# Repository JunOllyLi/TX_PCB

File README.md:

NOTE: the latest PCB had been manufactured was v2.0. But it had the Gimbal ZH-connector reversed. The schematics and PCB drawing had been updated to v2.1 to fix that. But v2.1 had not been really manufactured yet.

By default, Muffin is designed to use FlySky hall gimblal, over UART. However, if any other gimbals can be used with two wires (4 including GND and 3.3V), SW can be modified to use that.

Two RF module interfaces were designed. Although the name of them are for INTMOD and EXTMOD, SW can totally choose how they were used. The default configuration has the ELRS module connected to INTMOD and 4in1 connected to EXTMOD.

Those two modules have their own individual 5V power supply, controled by SW.
The PPM in/out on the back of FS6 shares the same signal pins of the EXTMOD.

And again, although the default design for them are UART and PPM, SW can totally choose other two wires protocol. ESP32 is very flexible regarding pin muxing.

# BOM (parts not listed in the schematics)
+ display module: IL9488 https://www.aliexpress.us/item/3256803764394132.html?spm=a2g0o.order_list.order_list_main.46.48c41802DB5b2D&gatewayAdapt=glo2usa
+ CPU ESP32S3 N16R8: https://www.aliexpress.us/item/3256805164206118.html?spm=a2g0o.order_list.order_list_main.61.48c41802DB5b2D&gatewayAdapt=glo2usa
+ Zorro 4in1 module
+ Zorro ELRS module

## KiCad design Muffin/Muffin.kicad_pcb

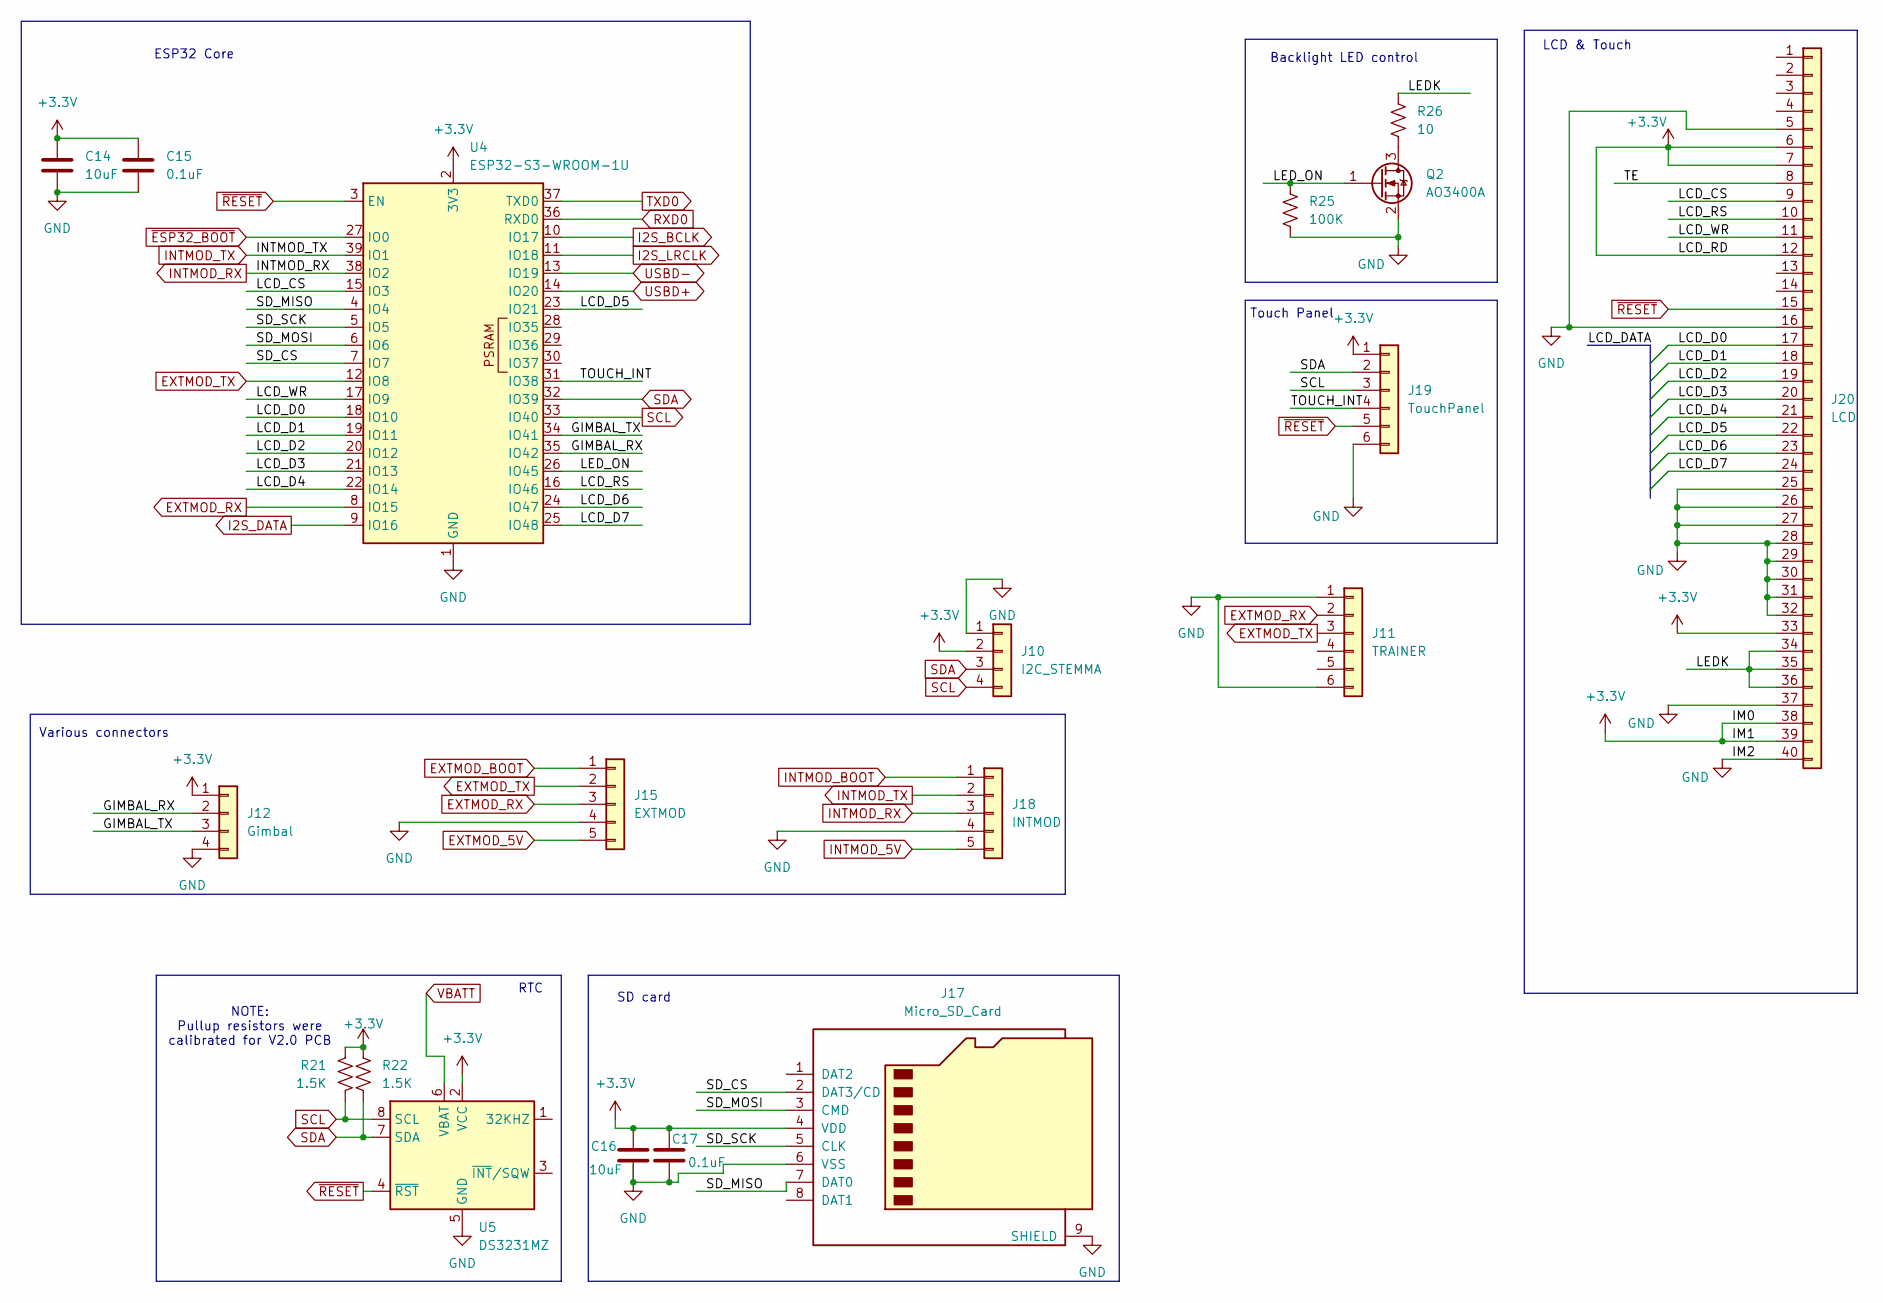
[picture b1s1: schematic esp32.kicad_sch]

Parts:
C14, C16: 10uF; C_0603_1608Metric
C15, C17: 0.1uF; C_0603_1608Metric
J10: I2C_STEMMA; JST_SH_BM04B-SRSS-TB_1x04-1MP_P1.00mm_Vertical
J11: TRAINER; JST_ZH1.50mm_6_PIN_Vertical
J12: Gimbal; JST_ZH_B4B-ZR-SM4-TF_1x04-1MP_P1.50mm_Vertical
J15: EXTMOD; Molex_PicoBlade_53398-0571_1x05-1MP_P1.25mm_Vertical
J17: Micro_SD_Card; MicroSD
J18: INTMOD; Molex_PicoBlade_53398-0571_1x05-1MP_P1.25mm_Vertical
J19: TouchPanel; FPC_6PIN_BOTTOM
J20: LCD; FPC_40PIN_TOP
Q2: AO3400A; SOT-23
R21, R22: 1.5K; R_0603_1608Metric
R25: 100K; R_0603_1608Metric
R26: 10; R_0603_1608Metric
U4: ESP32-S3-WROOM-1U
U5: DS3231MZ; SOIC-8_3.9x4.9mm_P1.27mm

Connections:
+3.3V: C14.1, C15.1, C16.1, C17.1, J10.2, J12.1, J17.4 (VDD), J19.1, J20.6, J20.7, J20.12, J20.33, J20.38, J20.39, R21.1, R22.1, U4.2 (3V3), U5.2 (VCC); also elsewhere on the board
/ESP32 Core/GIMBAL_RX: J12.2, U4.35 (IO42)
/ESP32 Core/GIMBAL_TX: J12.3, U4.34 (IO41)
/ESP32 Core/LCD_CS: J20.9, U4.15 (IO3)
/ESP32 Core/LCD_D0: J20.17, U4.18 (IO10)
/ESP32 Core/LCD_D1: J20.18, U4.19 (IO11)
/ESP32 Core/LCD_D2: J20.19, U4.20 (IO12)
/ESP32 Core/LCD_D3: J20.20, U4.21 (IO13)
/ESP32 Core/LCD_D4: J20.21, U4.22 (IO14)
/ESP32 Core/LCD_D5: J20.22, U4.23 (IO21)
/ESP32 Core/LCD_D6: J20.23, U4.24 (IO47)
/ESP32 Core/LCD_D7: J20.24, U4.25 (IO48)
/ESP32 Core/LCD_RS: J20.10, U4.16 (IO46)
/ESP32 Core/LCD_WR: J20.11, U4.17 (IO9)
/ESP32 Core/LEDK: J20.34, J20.35, J20.36, R26.1
/ESP32 Core/LED_ON: Q2.1 (G), R25.1, U4.26 (IO45)
/ESP32 Core/SD_CS: J17.2 (DAT3/CD), U4.7 (IO7)
/ESP32 Core/SD_MISO: J17.7 (DAT0), U4.4 (IO4)
/ESP32 Core/SD_MOSI: J17.3 (CMD), U4.6 (IO6)
/ESP32 Core/SD_SCK: J17.5 (CLK), U4.5 (IO5)
/ESP32 Core/TE: J20.8
/ESP32 Core/TOUCH_INT: J19.4, U4.31 (IO38)
EXTMOD_5V: J15.5; also elsewhere on the board
EXTMOD_BOOT: J15.1; also elsewhere on the board
EXTMOD_RX: J11.2, J15.3, U4.8 (IO15)
EXTMOD_TX: J11.3, J15.2, U4.12 (IO8)
GND: C14.2, C15.2, C16.2, C17.2, J10.1, J11.1, J11.6, J12.4, J15.4, J17.6 (VSS), J17.9 (SHIELD), J18.4, J19.6, J20.5, J20.16, J20.25, J20.26, J20.27, J20.28, J20.29, J20.30, J20.31, J20.32, J20.37, J20.40, Q2.2 (S), R25.2, U4.1 (GND), U4.40 (GND), U4.41 (GND), U5.5 (GND); also elsewhere on the board
I2S_BCLK: U4.10 (IO17); also elsewhere on the board
I2S_DATA: U4.9 (IO16); also elsewhere on the board
I2S_LRCLK: U4.11 (IO18); also elsewhere on the board
INTMOD_5V: J18.5; also elsewhere on the board
INTMOD_BOOT: J18.1; also elsewhere on the board
INTMOD_RX: J18.3, U4.38 (IO2)
INTMOD_TX: J18.2, U4.39 (IO1)
unnamed: Q2.3 (D), R26.2
RXD0: U4.36 (RXD0); also elsewhere on the board
SCL: J10.4, J19.3, R21.2, U4.33 (IO40), U5.8 (SCL); also elsewhere on the board
SDA: J10.3, J19.2, R22.2, U4.32 (IO39), U5.7 (SDA); also elsewhere on the board
TXD0: U4.37 (TXD0); also elsewhere on the board
USBD+: U4.14 (IO20); also elsewhere on the board
USBD-: U4.13 (IO19); also elsewhere on the board
VBATT: U5.6 (VBAT); also elsewhere on the board
~ESP32_BOOT: U4.27 (IO0); also elsewhere on the board
~RESET: J19.5, J20.15, U4.3 (EN), U5.4 (~RST); also elsewhere on the board

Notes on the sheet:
Touch Panel
NOTE: Pullup resistors were calibrated for V2.0 PCB
ESP32 Core
Backlight LED control
Various connectors
RTC
LCD & Touch
SD card

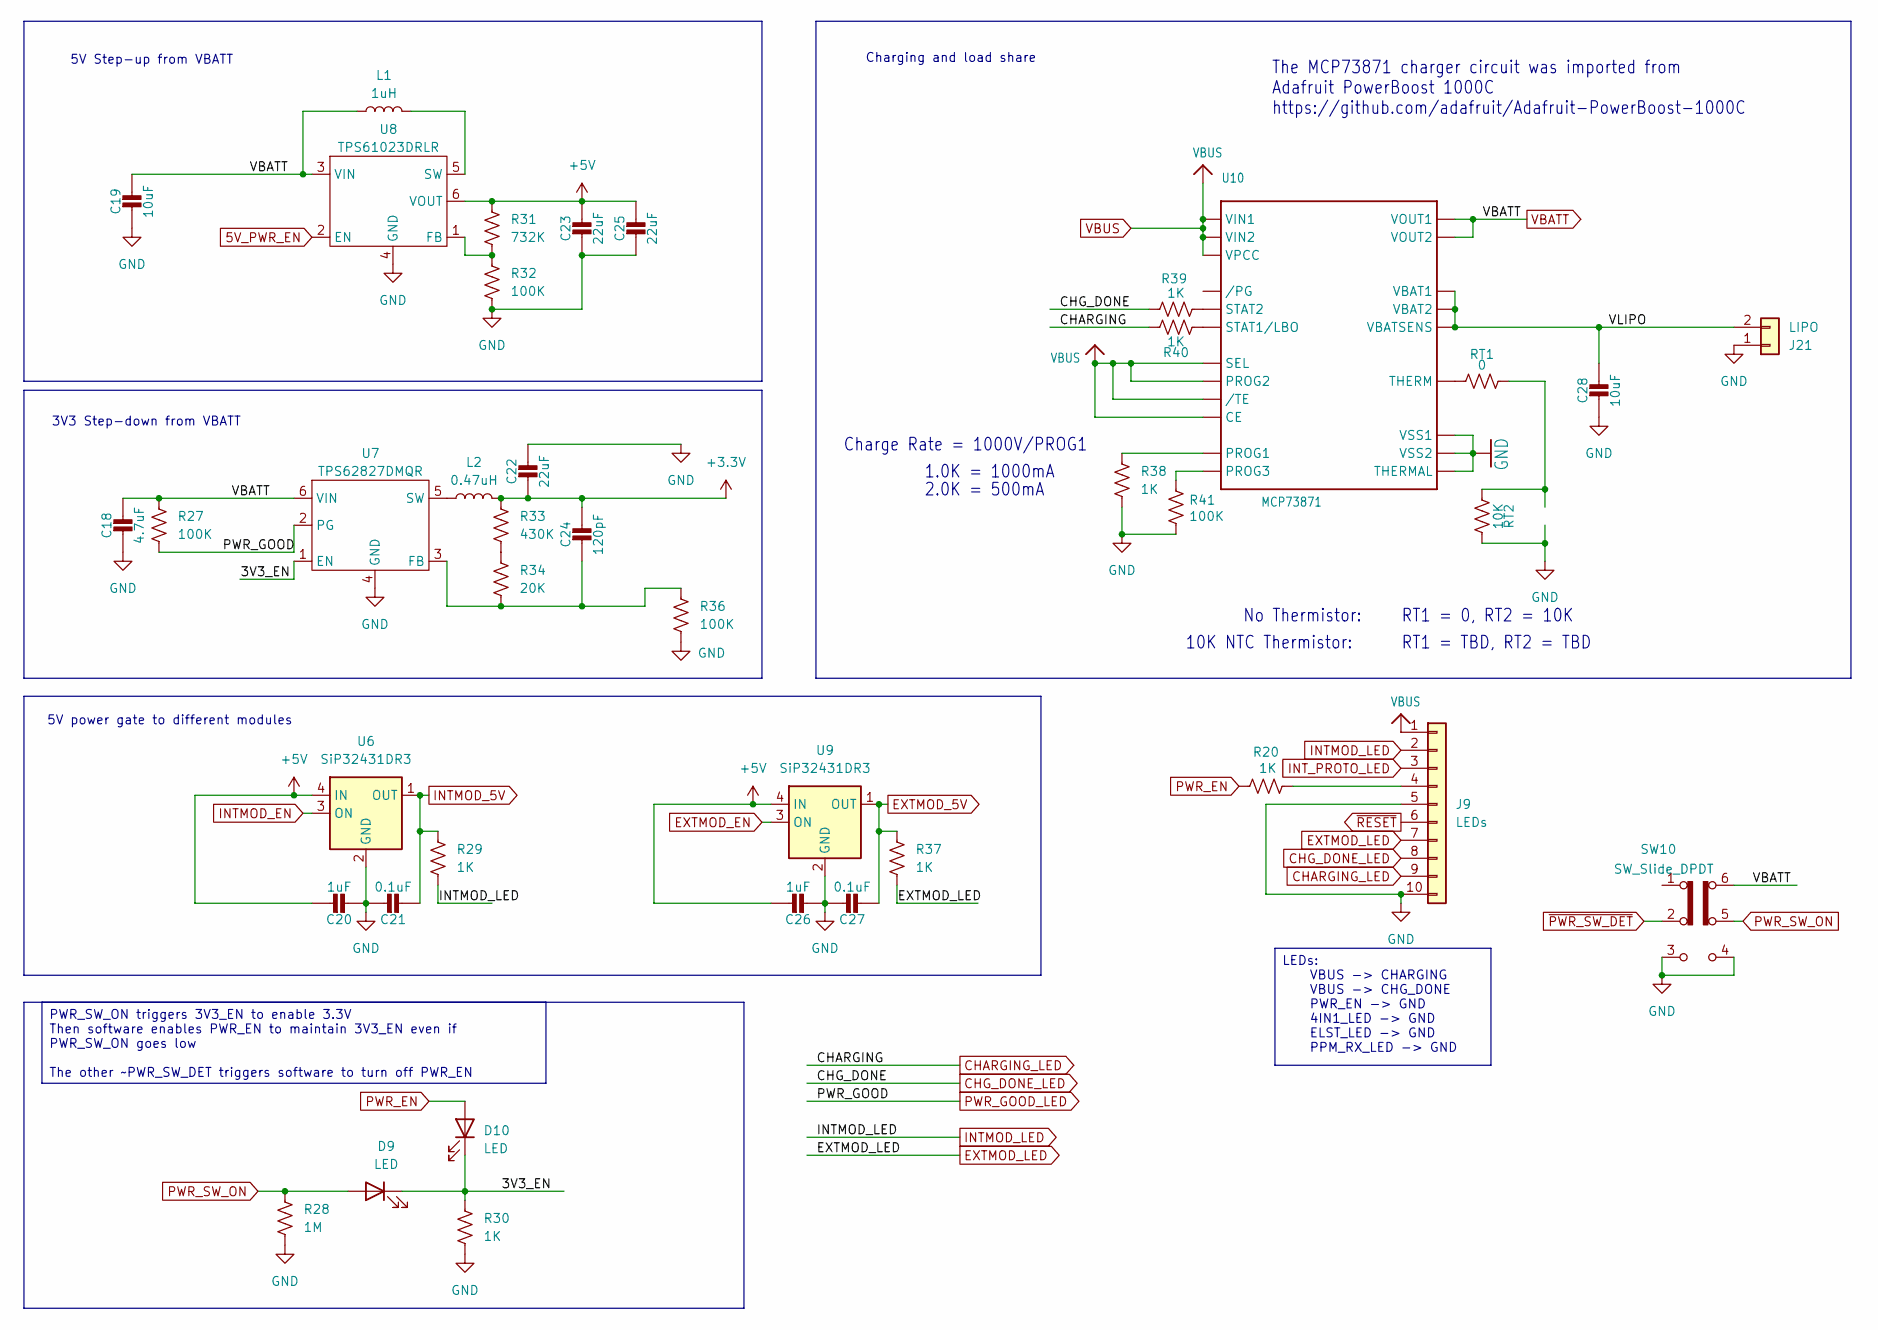
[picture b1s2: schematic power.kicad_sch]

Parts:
C18: 4.7uF; C_0603_1608Metric
C19, C28: 10uF; C_0603_1608Metric
C20, C26: 1uF; C_0603_1608Metric
C21, C27: 0.1uF; C_0603_1608Metric
C22, C23, C25: 22uF; C_0603_1608Metric
C24: 120pF; C_0603_1608Metric
D9, D10: LED; LED_0603_1608Metric
J9: LEDs; JST_GH_BM10B-GHS-TBT_1x10-1MP_P1.25mm_Vertical
J21: LIPO; AMASS_XT30UPB-M_1x02_P5.0mm_Vertical
L1: 1uH; L_Cenker_CKCS4020
L2: 0.47uH; L_Cenker_CKCS4020
R20, R29, R30, R37, R38, R39, R40: 1K; R_0603_1608Metric
R27, R32, R36, R41: 100K; R_0603_1608Metric
R28: 1M; R_0603_1608Metric
R31: 732K; R_0603_1608Metric
R33: 430K; R_0603_1608Metric
R34: 20K; R_0603_1608Metric
RT1: 0; R_0603_1608Metric
RT2: 10K; R_0603_1608Metric
SW10: SW_Slide_DPDT; SW_SLIDE_DPDT_7mm
U6, U9: SiP32431DR3; SOT-363_SC-70-6
U7: TPS62827DMQR; DMQ_6
U8: TPS61023DRLR; Texas_R-PDSO-N6_DRL-6
U10: MCP73871; QFN-20-1EP_4x4mm_P0.5mm_EP2.5x2.5mm

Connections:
5V_PWR_EN: U8.2 (EN); also elsewhere on the board
+3.3V: C22.2, C24.1, L2.2, R33.1; also elsewhere on the board
+5V: C20.1, C23.1, C25.1, C26.1, R31.1, U6.4 (IN), U8.6 (VOUT), U9.4 (IN); also elsewhere on the board
/Power/3V3_EN: D9.1 (K), D10.1 (K), R30.1, U7.1 (EN)
/Power/VLIPO: C28.1, J21.2, U10.14 (VBAT1), U10.15 (VBAT2), U10.16 (VBATSENS)
CHARGING_LED: J9.9, R40.1
CHG_DONE_LED: J9.8, R39.1
EXTMOD_5V: C27.2, R37.1, U9.1 (OUT); also elsewhere on the board
EXTMOD_EN: U9.3 (ON); also elsewhere on the board
EXTMOD_LED: J9.7, R37.2
GND: C18.2, C19.2, C20.2, C21.1, C22.1, C23.2, C25.2, C26.2, C27.1, C28.2, J9.5, J9.10, J21.1, R28.2, R30.2, R32.2, R36.2, R38.2, R41.2, RT2.2, SW10.3 (C), SW10.4 (A), U6.2 (GND), U6.5 (GND), U7.4 (GND), U8.4 (GND), U9.2 (GND), U9.5 (GND), U10.10 (VSS1), U10.11 (VSS2), U10.21 (THERMAL); also elsewhere on the board
INTMOD_5V: C21.2, R29.1, U6.1 (OUT); also elsewhere on the board
INTMOD_EN: U6.3 (ON); also elsewhere on the board
INTMOD_LED: J9.2, R29.2
INT_PROTO_LED: J9.3; also elsewhere on the board
unnamed: J9.4, R20.1
unnamed: R33.2, R34.1
unnamed: RT1.2, RT2.1
unnamed: C24.2, R34.2, R36.1, U7.3 (FB)
unnamed: L2.1, U7.5 (SW)
unnamed: R31.2, R32.1, U8.1 (FB)
unnamed: L1.2, U8.5 (SW)
unnamed: R38.1, U10.13 (PROG1)
unnamed: R41.1, U10.12 (PROG3)
unnamed: R40.2, U10.8 (STAT1/LBO)
unnamed: R39.2, U10.7 (STAT2)
unnamed: RT1.1, U10.5 (THERM)
PWR_EN: D10.2 (A), R20.2; also elsewhere on the board
PWR_GOOD_LED: R27.2, U7.2 (PG)
PWR_SW_ON: D9.2 (A), R28.1, SW10.5 (B)
VBATT: C18.1, C19.1, L1.1, R27.1, SW10.6 (C), U7.6 (VIN), U8.3 (VIN), U10.1 (VOUT1), U10.20 (VOUT2); also elsewhere on the board
VBUS: J9.1, U10.2 (VPCC), U10.3 (SEL), U10.4 (PROG2), U10.9 (/TE), U10.17 (CE), U10.18 (VIN1), U10.19 (VIN2); also elsewhere on the board
~PWR_SW_DET: SW10.2 (B); also elsewhere on the board
~RESET: J9.6; also elsewhere on the board

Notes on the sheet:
10K NTC Thermistor:
5V power gate to different modules
The MCP73871 charger circuit was imported from Adafruit PowerBoost 1000C https://github.com/adafruit/Adafruit-PowerBoost-1000C
5V Step-up from VBATT
1.0K = 1000mA
No Thermistor:
Charge Rate = 1000V/PROG1
RT1 = TBD, RT2 = TBD
Charging and load share
3V3 Step-down from VBATT
RT1 = 0, RT2 = 10K
2.0K = 500mA
LEDs: VBUS -> CHARGING VBUS -> CHG_DONE PWR_EN -> GND 4IN1_LED -> GND ELST_LED -> GND PPM_RX_LED -> GND
PWR_SW_ON triggers 3V3_EN to enable 3.3V Then software enables PWR_EN to maintain 3V3_EN even if PWR_SW_ON goes low The other ~PWR_SW_DET triggers software to turn off PWR_EN

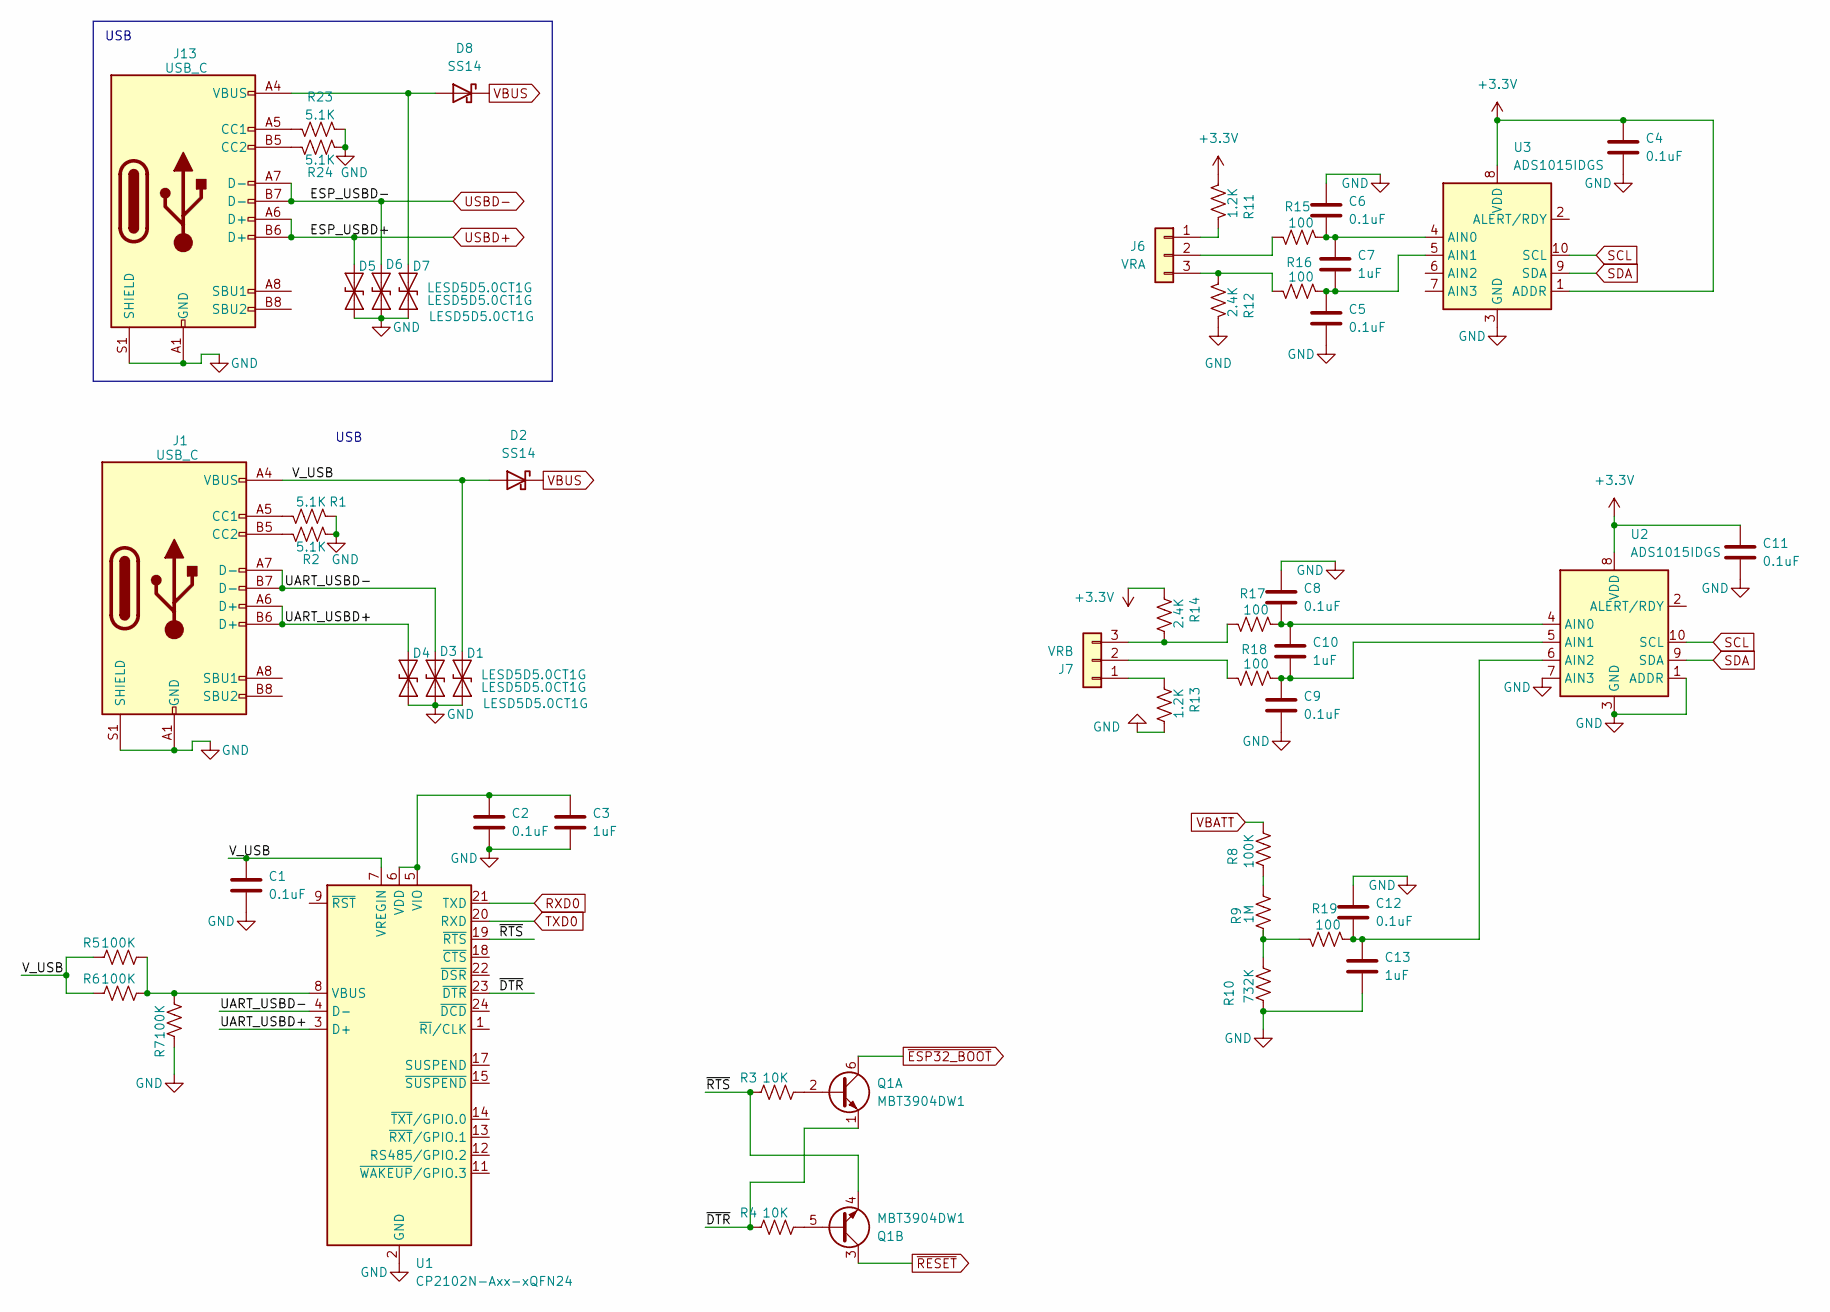
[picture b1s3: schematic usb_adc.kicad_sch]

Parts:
C1, C2, C4, C5, C6, C8, C9, C11, C12: 0.1uF; C_0603_1608Metric
C3, C7, C10, C13: 1uF; C_0603_1608Metric
D1, D3, D4, D5, D6, D7: LESD5D5.0CT1G; D_SOD-523
D2, D8: SS14; D_SMA
J1, J13: USB_C; my_USB_C_Receptacle_GCT_USB4105-xx-A_16P_TopMnt_Horizontal
J6: VRA; JST_GH_BM03B-GHS-TBT_1x03-1MP_P1.25mm_Vertical
J7: VRB; JST_GH_BM03B-GHS-TBT_1x03-1MP_P1.25mm_Vertical
Q1: MBT3904DW1; SOT-363_SC-70-6
R1, R2, R23, R24: 5.1K; R_0603_1608Metric
R3, R4: 10K; R_0603_1608Metric
R5, R6, R7, R8: 100K; R_0603_1608Metric
R9: 1M; R_0603_1608Metric
R10: 732K; R_0603_1608Metric
R11, R13: 1.2K; R_0603_1608Metric
R12, R14: 2.4K; R_0603_1608Metric
R15, R16, R17, R18, R19: 100; R_0603_1608Metric
U1: CP2102N-Axx-xQFN24; QFN-24-1EP_4x4mm_P0.5mm_EP2.6x2.6mm
U2, U3: ADS1015IDGS; TSSOP-10_3x3mm_P0.5mm

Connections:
+3.3V: C4.1, C11.1, R11.2, R14.1, U2.8 (VDD), U3.1 (ADDR), U3.8 (VDD); also elsewhere on the board
/USB and ADC/UART_USBD+: D4.2 (A2), J1.A6 (D+), J1.B6 (D+), U1.3 (D+)
/USB and ADC/UART_USBD-: D3.2 (A2), J1.A7 (D-), J1.B7 (D-), U1.4 (D-)
/USB and ADC/V_USB: C1.1, D1.2 (A2), D2.2 (A), J1.A4 (VBUS), J1.A9 (VBUS), J1.B4 (VBUS), J1.B9 (VBUS), R5.1, R6.1, U1.7 (VREGIN)
/USB and ADC/~DTR: Q1.1 (E1), R4.1, U1.23 (~DTR)
/USB and ADC/~RTS: Q1.4 (E2), R3.1, U1.19 (~RTS)
GND: C1.2, C2.2, C3.2, C4.2, C5.2, C6.1, C8.1, C9.2, C11.2, C12.1, C13.2, D1.1 (A1), D3.1 (A1), D4.1 (A1), D5.1 (A1), D6.1 (A1), D7.1 (A1), J1.A1 (GND), J1.A12 (GND), J1.B1 (GND), J1.B12 (GND), J1.S1 (SHIELD), J13.A1 (GND), J13.A12 (GND), J13.B1 (GND), J13.B12 (GND), J13.S1 (SHIELD), R1.1, R2.1, R7.1, R10.1, R12.1, R13.2, R23.1, R24.1, U1.2 (GND), U1.25 (GND), U2.1 (ADDR), U2.3 (GND), U2.7 (AIN3), U3.3 (GND); also elsewhere on the board
unnamed: D7.2 (A2), D8.2 (A), J13.A4 (VBUS), J13.A9 (VBUS), J13.B4 (VBUS), J13.B9 (VBUS)
unnamed: J1.A5 (CC1), R1.2
unnamed: J1.B5 (CC2), R2.2
unnamed: J6.1, R11.1
unnamed: J6.2, R15.2
unnamed: J6.3, R12.2, R16.2
unnamed: J7.1, R13.1
unnamed: J7.2, R18.2
unnamed: J7.3, R14.2, R17.2
unnamed: J13.A5 (CC1), R23.2
unnamed: J13.B5 (CC2), R24.2
unnamed: Q1.2 (B1), R3.2
unnamed: Q1.5 (B2), R4.2
unnamed: R8.1, R9.2
unnamed: R9.1, R10.2, R19.2
unnamed: R5.2, R6.2, R7.2, U1.8 (VBUS)
unnamed: C2.1, C3.1, U1.5 (VIO), U1.6 (VDD)
unnamed: C8.2, C10.1, R17.1, U2.4 (AIN0)
unnamed: C9.1, C10.2, R18.1, U2.5 (AIN1)
unnamed: C12.2, C13.1, R19.1, U2.6 (AIN2)
unnamed: C6.2, C7.1, R15.1, U3.4 (AIN0)
unnamed: C5.1, C7.2, R16.1, U3.5 (AIN1)
RXD0: U1.21 (TXD); also elsewhere on the board
SCL: U2.10 (SCL), U3.10 (SCL); also elsewhere on the board
SDA: U2.9 (SDA), U3.9 (SDA); also elsewhere on the board
TXD0: U1.20 (RXD); also elsewhere on the board
USBD+: D5.2 (A2), J13.A6 (D+), J13.B6 (D+); also elsewhere on the board
USBD-: D6.2 (A2), J13.A7 (D-), J13.B7 (D-); also elsewhere on the board
VBATT: R8.2; also elsewhere on the board
VBUS: D2.1 (K), D8.1 (K); also elsewhere on the board
~ESP32_BOOT: Q1.6 (C1); also elsewhere on the board
~RESET: Q1.3 (C2); also elsewhere on the board

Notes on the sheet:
USB

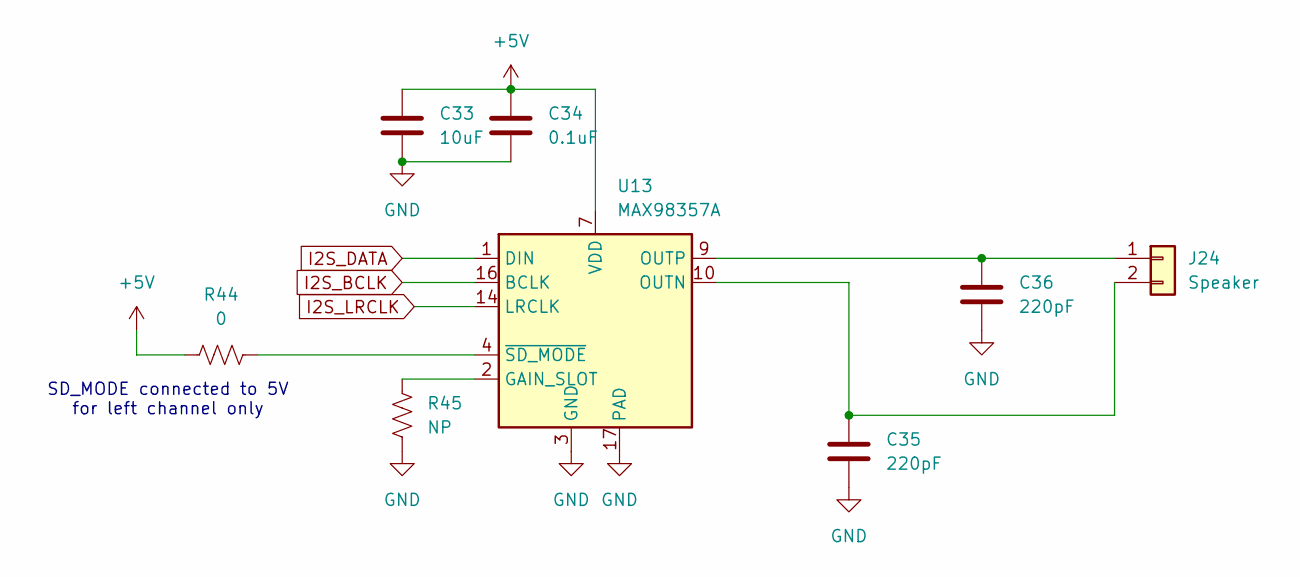
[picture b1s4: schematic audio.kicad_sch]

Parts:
C33: 10uF; C_0603_1608Metric
C34: 0.1uF; C_0603_1608Metric
C35, C36: 220pF; C_0603_1608Metric
J24: Speaker; Molex_PicoBlade_53398-0271_1x02-1MP_P1.25mm_Vertical
R44: 0; R_0603_1608Metric
R45: NP; R_0603_1608Metric
U13: MAX98357A; TQFN-16-1EP_3x3mm_P0.5mm_EP1.23x1.23mm

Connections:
+5V: C33.1, C34.1, R44.1, U13.7 (VDD), U13.8 (VDD); also elsewhere on the board
GND: C33.2, C34.2, C35.2, C36.2, R45.1, U13.3 (GND), U13.11 (GND), U13.15 (GND), U13.17 (PAD); also elsewhere on the board
I2S_BCLK: U13.16 (BCLK); also elsewhere on the board
I2S_DATA: U13.1 (DIN); also elsewhere on the board
I2S_LRCLK: U13.14 (LRCLK); also elsewhere on the board
unnamed: C36.1, J24.1, U13.9 (OUTP)
unnamed: C35.1, J24.2, U13.10 (OUTN)
unnamed: R45.2, U13.2 (GAIN_SLOT)
unnamed: R44.2, U13.4 (~SD_MODE)

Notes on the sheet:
SD_MODE connected to 5V for left channel only

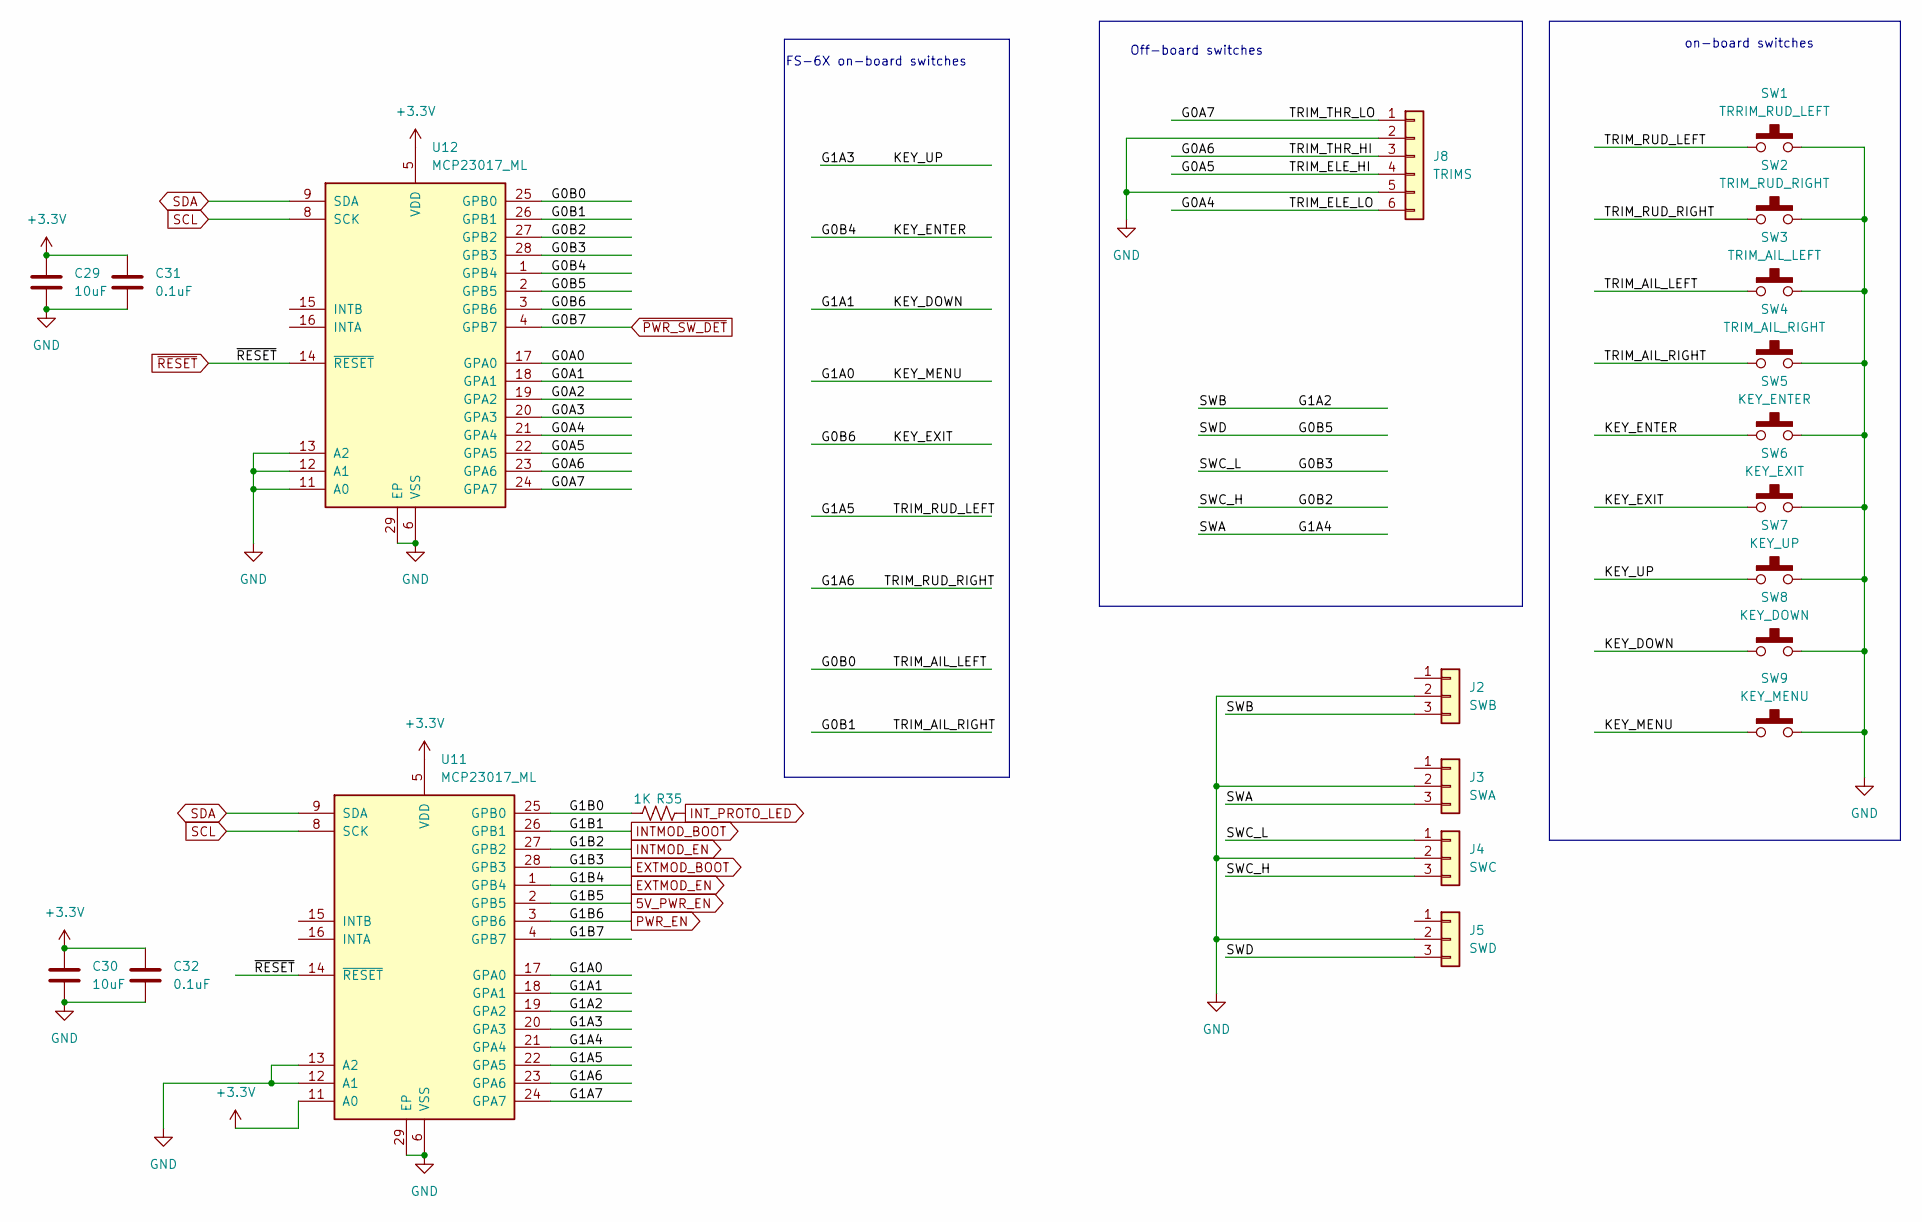
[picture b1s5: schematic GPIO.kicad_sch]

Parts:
C29, C30: 10uF; C_0603_1608Metric
C31, C32: 0.1uF; C_0603_1608Metric
J2: SWB; JST_GH_BM03B-GHS-TBT_1x03-1MP_P1.25mm_Vertical
J3: SWA; JST_GH_BM03B-GHS-TBT_1x03-1MP_P1.25mm_Vertical
J4: SWC; JST_GH_BM03B-GHS-TBT_1x03-1MP_P1.25mm_Vertical
J5: SWD; JST_GH_BM03B-GHS-TBT_1x03-1MP_P1.25mm_Vertical
J8: TRIMS; JST_ZH1.50mm_6_PIN_Vertical
R35: 1K; R_0603_1608Metric
SW1: TRRIM_RUD_LEFT; SW_6.2mm
SW2: TRIM_RUD_RIGHT; SW_6.2mm
SW3: TRIM_AIL_LEFT; SW_6.2mm
SW4: TRIM_AIL_RIGHT; SW_6.2mm
SW5: KEY_ENTER; SW_6.2mm
SW6: KEY_EXIT; SW_6.2mm
SW7: KEY_UP; SW_6.2mm
SW8: KEY_DOWN; SW_6.2mm
SW9: KEY_MENU; SW_12mm
U11, U12: MCP23017_ML; QFN-28-1EP_6x6mm_P0.65mm_EP4.25x4.25mm

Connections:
5V_PWR_EN: U11.2 (GPB5); also elsewhere on the board
+3.3V: C29.1, C30.1, C31.1, C32.1, U11.5 (VDD), U11.11 (A0), U12.5 (VDD); also elsewhere on the board
/GPIO_ext/G0A0: U12.17 (GPA0)
/GPIO_ext/G0A1: U12.18 (GPA1)
/GPIO_ext/G0A2: U12.19 (GPA2)
/GPIO_ext/G0A3: U12.20 (GPA3)
/GPIO_ext/G0A4: J8.6, U12.21 (GPA4)
/GPIO_ext/G0A5: J8.4, U12.22 (GPA5)
/GPIO_ext/G0A6: J8.3, U12.23 (GPA6)
/GPIO_ext/G0A7: J8.1, U12.24 (GPA7)
/GPIO_ext/G0B0: SW3.1 (A), SW3.2 (B), U12.25 (GPB0)
/GPIO_ext/G0B1: SW4.1 (A), SW4.2 (B), U12.26 (GPB1)
/GPIO_ext/G0B2: J4.3, U12.27 (GPB2)
/GPIO_ext/G0B3: J4.1, U12.28 (GPB3)
/GPIO_ext/G0B4: SW5.1 (A), SW5.2 (B), U12.1 (GPB4)
/GPIO_ext/G0B5: J5.3, U12.2 (GPB5)
/GPIO_ext/G0B6: SW6.1 (A), SW6.2 (B), U12.3 (GPB6)
/GPIO_ext/G1A0: SW9.1 (A), SW9.2 (B), U11.17 (GPA0)
/GPIO_ext/G1A1: SW8.1 (A), SW8.2 (B), U11.18 (GPA1)
/GPIO_ext/G1A2: J2.3, U11.19 (GPA2)
/GPIO_ext/G1A3: SW7.1 (A), SW7.2 (B), U11.20 (GPA3)
/GPIO_ext/G1A4: J3.3, U11.21 (GPA4)
/GPIO_ext/G1A5: SW1.1 (A), SW1.2 (B), U11.22 (GPA5)
/GPIO_ext/G1A6: SW2.1 (A), SW2.2 (B), U11.23 (GPA6)
/GPIO_ext/G1A7: U11.24 (GPA7)
/GPIO_ext/G1B0: R35.1, U11.25 (GPB0)
/GPIO_ext/G1B7: U11.4 (GPB7)
EXTMOD_BOOT: U11.28 (GPB3); also elsewhere on the board
EXTMOD_EN: U11.1 (GPB4); also elsewhere on the board
GND: C29.2, C30.2, C31.2, C32.2, J2.2, J3.2, J4.2, J5.2, J8.2, J8.5, SW1.3 (C), SW1.4 (D), SW2.3 (C), SW2.4 (D), SW3.3 (C), SW3.4 (D), SW4.3 (C), SW4.4 (D), SW5.3 (C), SW5.4 (D), SW6.3 (C), SW6.4 (D), SW7.3 (C), SW7.4 (D), SW8.3 (C), SW8.4 (D), SW9.3 (C), SW9.4 (D), U11.6 (VSS), U11.12 (A1), U11.13 (A2), U11.29 (EP), U12.6 (VSS), U12.11 (A0), U12.12 (A1), U12.13 (A2), U12.29 (EP); also elsewhere on the board
INTMOD_BOOT: U11.26 (GPB1); also elsewhere on the board
INTMOD_EN: U11.27 (GPB2); also elsewhere on the board
INT_PROTO_LED: R35.2; also elsewhere on the board
PWR_EN: U11.3 (GPB6); also elsewhere on the board
SCL: U11.8 (SCK), U12.8 (SCK); also elsewhere on the board
SDA: U11.9 (SDA), U12.9 (SDA); also elsewhere on the board
~PWR_SW_DET: U12.4 (GPB7); also elsewhere on the board
~RESET: U11.14 (~RESET), U12.14 (~RESET); also elsewhere on the board

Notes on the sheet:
Off-board switches
on-board switches
FS-6X on-board switches

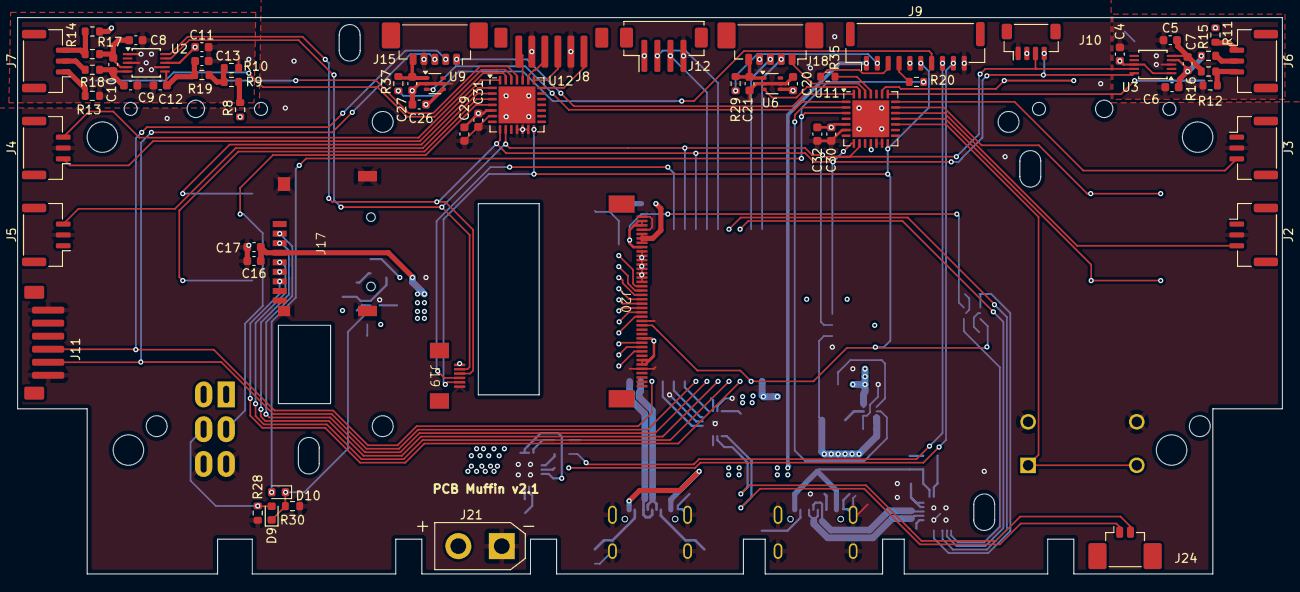
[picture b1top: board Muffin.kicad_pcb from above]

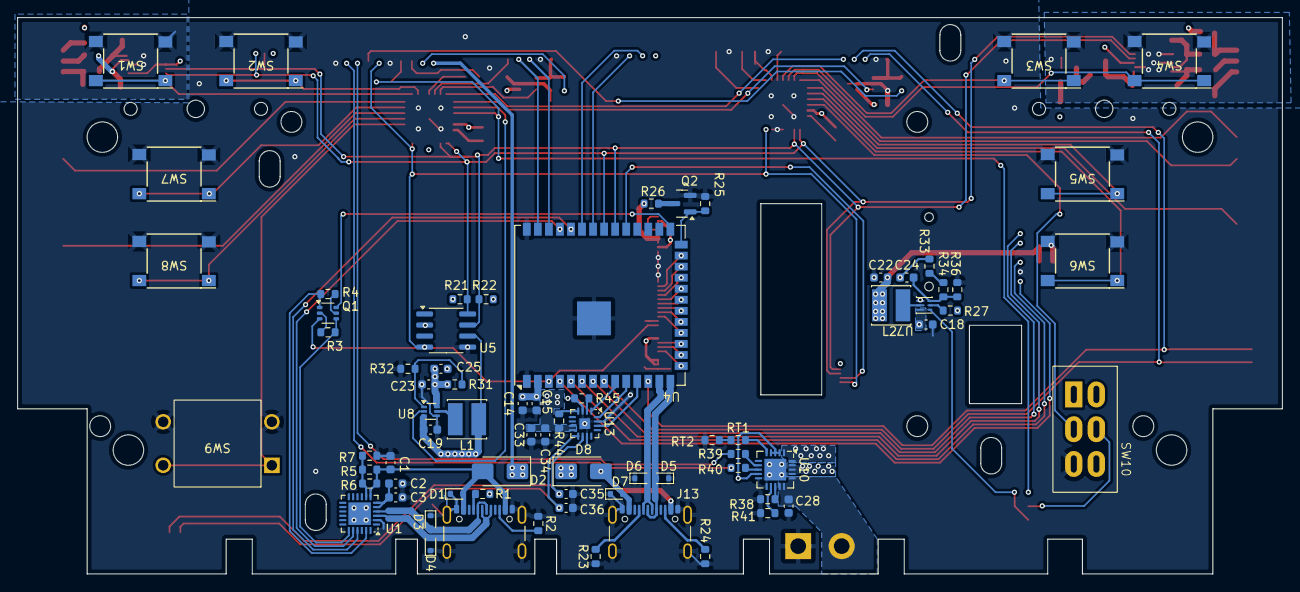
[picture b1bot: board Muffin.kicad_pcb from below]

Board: 4 copper layers, 145.4 x 64.0 mm, 138 parts (74 on the bottom side), 121 nets.
